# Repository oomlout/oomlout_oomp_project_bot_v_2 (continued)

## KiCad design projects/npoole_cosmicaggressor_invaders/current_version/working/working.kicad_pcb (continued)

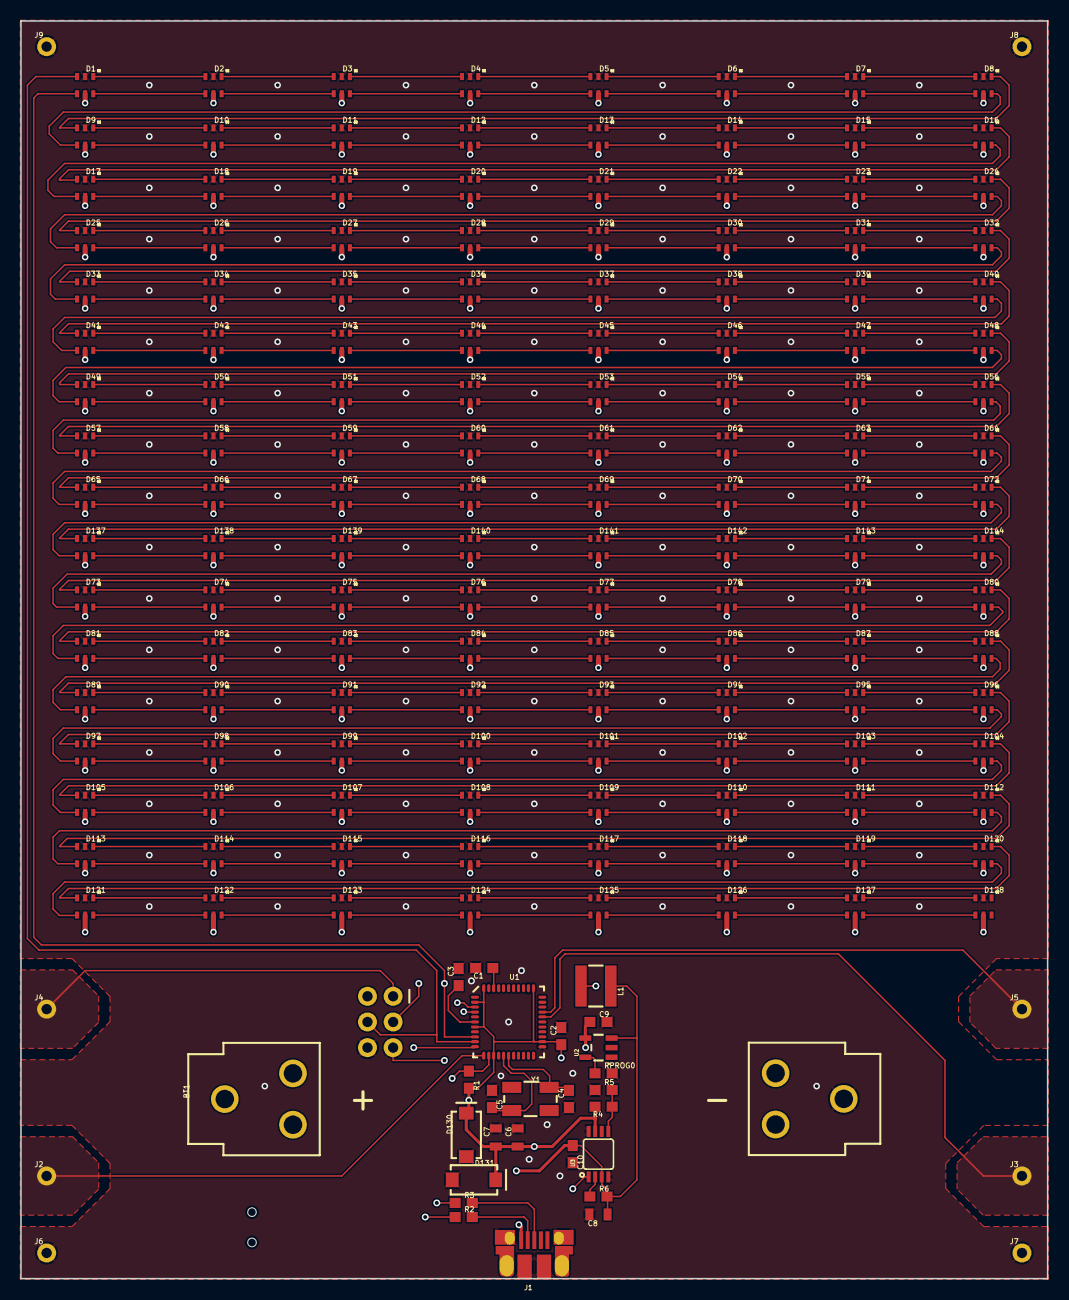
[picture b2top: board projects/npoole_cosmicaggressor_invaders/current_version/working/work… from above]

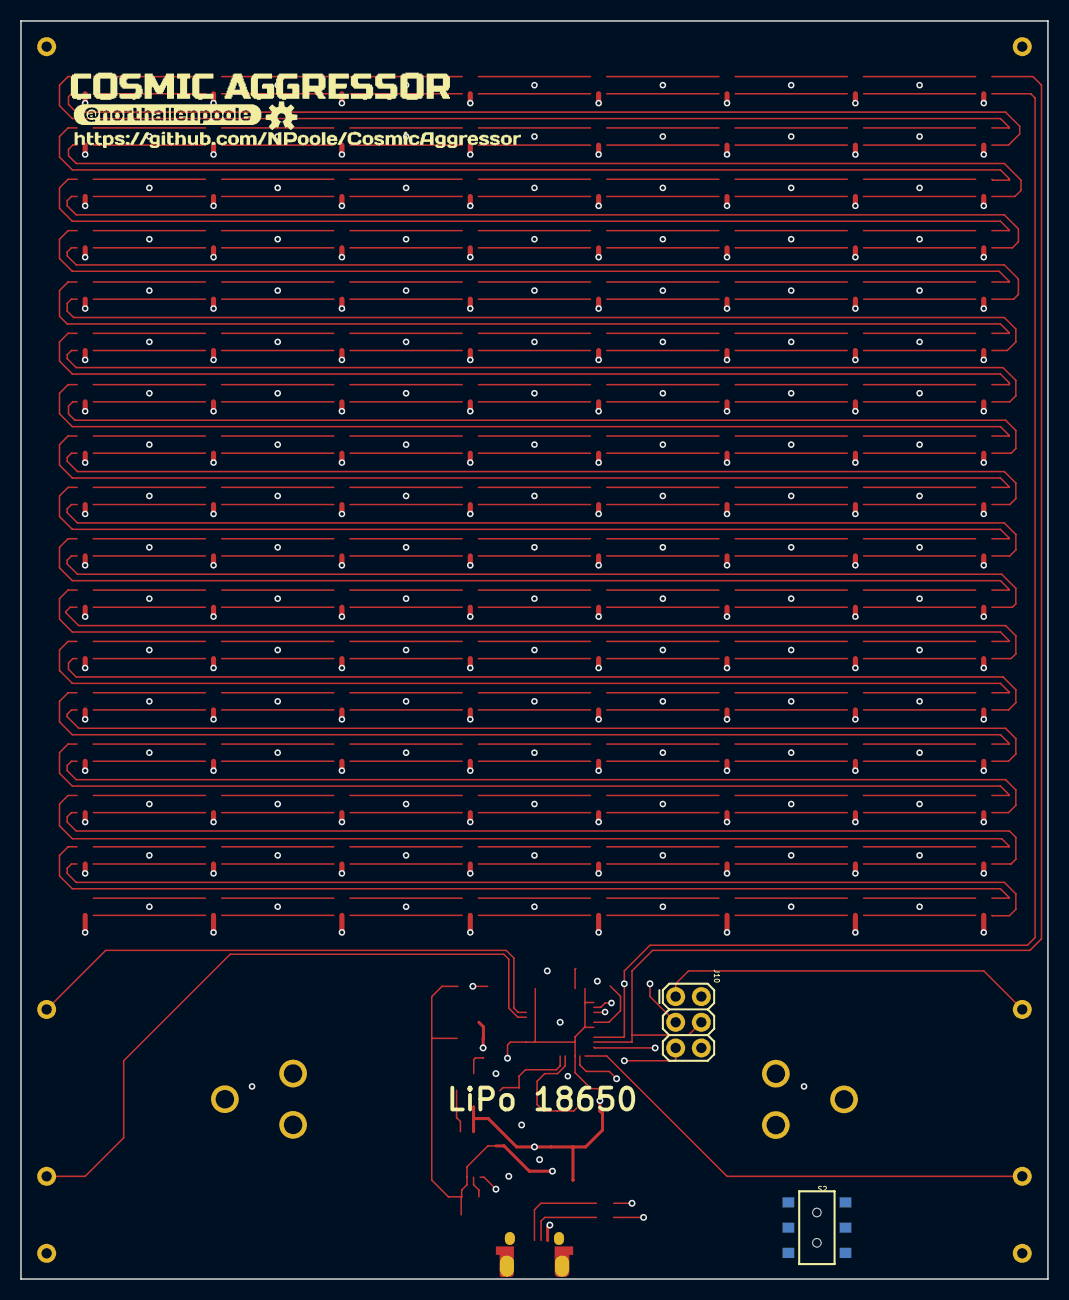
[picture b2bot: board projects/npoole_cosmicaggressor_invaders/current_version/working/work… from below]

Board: 4 copper layers, 101.6 x 124.5 mm, 176 parts (6 on the bottom side), 294 nets.

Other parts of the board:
U$1: COSMIC_AGGRESSOR0
U$2: #NORTHALLENPOOLE1
U$3: HTTPS###GITHUB#COM#NPOOLE#COSMICAGGRESSOR2
U$4: OSHW-LOGO-S

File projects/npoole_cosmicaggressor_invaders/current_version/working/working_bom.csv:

"Id";"Designator";"Footprint";"Quantity";"Designation";"Supplier and ref";
1;"D72,D84,D8,D46,D67,D22,D29,D92,D126,D20,D68,D66,D52,D87,D108,D99,D95,D2,D57,D100,D127,D120,D117,D38,D102,D137,D31,D61,D17,D3,D65,D121,D37,D30,D85,D103,D98,D33,D140,D79,D41,D1,D81,D77,D40,D11,D75,D19,D47,D74,D62,D49,D93,D128,D109,D141,D143,D42,D56,D54,D71,D115,D78,D111,D124,D114,D110,D50,D144,D24,D26,D5,D107,D35,D4,D76,D43,D28,D7,D104,D45,D101,D63,D90,D122,D60,D51,D15,D55,D16,D116,D48,D39,D80,D34,D23,D32,D123,D112,D12,D96,D105,D10,D142,D58,D113,D9,D25,D125,D106,D94,D53,D86,D139,D36,D118,D18,D44,D13,D64,D73,D59,D138,D69,D21,D6,D27,D82,D70,D119,D91,D89,D97,D88,D83,D14";"APA102-2020";136;"APA102-2020";;;
2;"C9,C10";"0603";2;"4.7uF";;;
3;"U2";"SOT23-5";1;"MCP73831";;;
4;"R3,R2";"0603@1";2;"22";;;
5;"Y1";"CRYSTAL-SMD-5X3.2-4PAD";1;"16MHz";;;
6;"R1";"0603@1";1;"10k";;;
7;"BT1";"BATTERY_18650-HOLDER";1;"";;;
8;"J9,J6,J5,J8,J4,J7,J2,J3";"1X01NS_KIT";8;"";;;
9;"D131,D130";"SMA-DIODE";2;"3A/40V/500mV";;;
10;"C2,C3";"0603";2;"1.0uF";;;
11;"C8,C6,C7";"0805";3;"22uF";;;
12;"C4,C5";"0603";2;"18pF";;;
13;"R6,R4";"0603";2;"750K";;;
14;"RPROG0";"0603";1;"2.0k";;;
15;"R5";"0603";1;"100k";;;
16;"C1";"0603";1;"0.1uF";;;
17;"U3";"MSOP8";1;"PAM2401";;;
18;"L1";"INDUCTOR_4X4MM";1;"2.2UH3A";;;
19;"J1";"USB-MICROB-PTH-MILL";1;"";;;
20;"U1";"QFN-44-NOPAD_1_1-LESS_PASTE";1;"32U4";;;
21;"S2";"SWITCH_DPDT_SMD_AYZ0202";1;"";;;
22;"U$1";"COSMIC_AGGRESSOR0";1;"";;;
23;"J10";"2X3";1;"AVR_SPI_PROG_3X2PTH";;;
24;"U$2";"#NORTHALLENPOOLE1";1;"";;;
25;"U$4";"OSHW-LOGO-S";1;"";;;
26;"U$3";"HTTPS###GITHUB#COM#NPOOLE#COSMICAGGRESSOR2";1;"";;;

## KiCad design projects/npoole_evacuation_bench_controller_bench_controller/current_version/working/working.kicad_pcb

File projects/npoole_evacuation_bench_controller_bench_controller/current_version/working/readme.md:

# evacuation_bench_controller
 
## summary 
* id: npoole_evacuation_bench_controller_bench_controller
* user: npoole
* name: evacuation_bench_controller
* board: bench_controller
* repo: https://github.com/NPoole/Evacuation_Bench_Controller

* src_file_repo_sch: 
* src_file_repo_sch_link: https://github.com/NPoole/Evacuation_Bench_Controller/tree/main/
* full details link: https://github.com/oomlout/oomlout_oomp_project_bot_v_2/tree/main/projects/npoole_evacuation_bench_controller_bench_controller/current_version/working  

## schematic  
  
[schematic (pdf)](working_schematic.pdf) 

## pcb  

[board (pdf)](working.pdf)  

## working_bom
| Id | Designator | Footprint | Quantity | Designation | Supplier and ref |  | None | 
| --- | --- | --- | --- | --- | --- | --- | --- | 
| 1 | U$23 | AUTO_EVAC0 | 1 |  |  |  | [''] | 
| 2 | D17,D18,D26,D13,D25,D19,D12,D10,D14,D22,D15,D24,D20,D21,D11,D16,D9 | APA102-2020 | 17 | APA102-2020 |  |  | [''] | 
| 3 | U$26 | EVAC_PORT0 | 1 |  |  |  | [''] | 
| 4 | S4,S5,S3,S8,S2,S7,S1 | CHERRY-MX-LED-1U | 7 | MECHANICAL-KEYBOARD1U |  |  | [''] | 
| 5 | U$18 | ROUGH_PUMP_ON0 | 1 |  |  |  | [''] | 
| 6 | U$27 | PRESSURE0 | 1 |  |  |  | [''] | 
| 7 | U$14 | EVAC_PORT_ISOLATE0 | 1 |  |  |  | [''] | 
| 8 | U$17 | TURBO_ON0 | 1 |  |  |  | [''] | 
| 9 | U$7 | AUX0 | 1 |  |  |  | [''] | 
| 10 | U$25,U$1 | ROUGH0 | 2 |  |  |  | [''] | 
| 11 | U$6 | PORT0 | 1 |  |  |  | [''] | 
| 12 | J13,J9,J11,J12,J4,J6,J5,J7 | 1X02_NO_SILK | 8 |  |  |  | [''] | 
| 13 | FRAME1 | CREATIVE_COMMONS | 1 | FRAME-LEDGER |  |  | [''] | 
| 14 | U$2 | TURBO0 | 1 |  |  |  | [''] | 
| 15 | U$50 | INTEG#SVG0 | 1 |  |  |  | [''] | 
| 16 | U$24,U$4 | VENT0 | 2 |  |  |  | [''] | 
| 17 | U$15 | FULL_VAC_OK0 | 1 |  |  |  | [''] | 
| 18 | U$29 | ROUGH_VAC0 | 1 |  |  |  | [''] | 
| 19 | U$10 | AUTO0 | 1 |  |  |  | [''] | 
| 20 | U$8 | ON0 | 1 |  |  |  | [''] | 
| 21 | U$20 | WATCHDOG_OK0 | 1 |  |  |  | [''] | 
| 22 | S6 | SWITCH_SPDT_PTH_11.6X4.0MM | 1 |  |  |  | [''] | 
| 23 | J10,J8,J2,J1,J3 | 1X03_NO_SILK | 5 |  |  |  | [''] | 
| 24 | U$12 | SHUT_DOWN0 | 1 |  |  |  | [''] | 
| 25 | U$28 | HIGH_VAC0 | 1 |  |  |  | [''] | 
| 26 | U$22 | ISOLATE0 | 1 |  |  |  | [''] | 
| 27 | D23 | LED_5MM | 1 |  |  |  | [''] | 
| 28 | U$11 | BRING_UP0 | 1 |  |  |  | [''] | 
| 29 | U$21 | WAIT_FOR_ION_GAUGE0 | 1 |  |  |  | [''] | 
| 30 | U$19 | TURBO_FULL_SPEED0 | 1 |  |  |  | [''] | 
| 31 | U$13 | SCRAM0 | 1 |  |  |  | [''] | 
| 32 | U$51 | EC#10 | 1 |  |  |  | [''] | 
| 33 | U$5 | EVAC0 | 1 |  |  |  | [''] | 
| 34 | U$16 | ROUGH_PRESSURE0 | 1 |  |  |  | [''] | 
| 35 | @HOLE0,@HOLE2,@HOLE1,@HOLE3 |  | 4 |  |  |  | [''] | 
| 36 | U$30 | AMBIENT0 | 1 |  |  |  | [''] | 
| 37 | U$3 | FORELINE0 | 1 |  |  |  | [''] | 
| 38 | U$9 | OFF0 | 1 |  |  |  | [''] | 
| 39 | U$33 | ADC30 | 1 |  |  |  | [''] | 
| 40 | R14,R7,R12,R15,R16,R9,R11,R5,R3,R13,R10 | 0603 | 11 | 10k |  |  | [''] | 
| 41 | D7,D6,D5,D8 | SOD-323 | 4 | 3A/10V/280mV |  |  | [''] | 
| 42 | Q2,Q1,Q3 | SO08 | 3 | 6.5A/30V/38mÎ© |  |  | [''] | 
| 43 | U$42,U$44,U$43,U$45 | _##10V##_0 | 4 |  |  |  | [''] | 
| 44 | U$36 | ADC00 | 1 |  |  |  | [''] | 
| 45 | R6,R8,R4 | 0603 | 3 | 1M |  |  | [''] | 
| 46 | U$34 | ADC20 | 1 |  |  |  | [''] | 
| 47 | U$31 | ADC50 | 1 |  |  |  | [''] | 
| 48 | D3,D4,D2 | SOD-323 | 3 | 250mA/100V |  |  | [''] | 
| 49 | U$49 | VALVE30 | 1 |  |  |  | [''] | 
| 50 | U$35 | ADC10 | 1 |  |  |  | [''] | 
| 51 | U$37 | GPIO00 | 1 |  |  |  | [''] | 
| 52 | B1 | UNO_R3_SHIELD_NOLABELS | 1 | ARDUINO_UNO_R3_SHIELDNOLABELS |  |  | [''] | 
| 53 | U$46 | 24VDC_IN0 | 1 |  |  |  | [''] | 
| 54 | R17 | 0603 | 1 | 1k |  |  | [''] | 
| 55 | U$39 | 5VDC_IN0 | 1 |  |  |  | [''] | 
| 56 | U$32 | ADC40 | 1 |  |  |  | [''] | 
| 57 | U$38 | GPIO10 | 1 |  |  |  | [''] | 
| 58 | U$48 | VALVE20 | 1 |  |  |  | [''] | 
| 59 | U$41,U$40 | _##5V##_0 | 2 |  |  |  | [''] | 
| 60 | U$47 | VALVE10 | 1 |  |  |  | [''] | 

## bom_schematic
| Ref | Qnty | Value | Cmp name | Footprint | Description | Vendor | DNP | 
| --- | --- | --- | --- | --- | --- | --- | --- | 
| B1 | 1 | ARDUINO_UNO_R3_SHIELDNOLABELS | ARDUINO_UNO_R3_SHIELDNOLABELS | working:UNO_R3_SHIELD_NOLABELS |  |  |  | 
| D2, D3, D4 | 3 | DIODE-BAS16J | DIODE-BAS16J | working:SOD-323 |  |  |  | 
| D5, D6, D7, D8 | 4 | 3A/10V/280mV | DIODE-SCHOTTKY-BAT60A | working:SOD-323 |  |  |  | 
| D9, D10, D11, D12, D13, D14, D15, D16, D17, D18, D19, D20, D21, D22, D24, D25, D26 | 17 | APA102-2020 | APA102-2020 | working:APA102-2020 |  |  |  | 
| D23 | 1 | LED5MM | LED5MM | working:LED_5MM |  |  |  | 
| FRAME1 | 1 | FRAME-LEDGER | FRAME-LEDGER | working:CREATIVE_COMMONS |  |  |  | 
| J1, J2, J3, J8, J10 | 5 | CONN_031X03_NO_SILK | CONN_031X03_NO_SILK | working:1X03_NO_SILK |  |  |  | 
| J4, J5, J6, J7, J9, J11, J12, J13 | 8 | CONN_021X02_NO_SILK | CONN_021X02_NO_SILK | working:1X02_NO_SILK |  |  |  | 
| Q1, Q2, Q3 | 3 | MOSFET-NCH-FDS6630A | MOSFET-NCH-FDS6630A | working:SO08 |  |  |  | 
| R3, R5, R7, R9, R10, R11, R12, R13, R14, R15, R16 | 11 | 10KOHM-0603-1/10W-1% | 10KOHM-0603-1/10W-1% | working:0603 |  |  |  | 
| R4, R6, R8 | 3 | 1MOHM-0603-1/4W-5% | 1MOHM-0603-1/4W-5% | working:0603 |  |  |  | 
| R17 | 1 | 1KOHM-0603-1/10W-1% | 1KOHM-0603-1/10W-1% | working:0603 |  |  |  | 
| S1, S2, S3, S4, S5, S7, S8 | 7 | MECHANICAL-KEYBOARD1U | MECHANICAL-KEYBOARD1U | working:CHERRY-MX-LED-1U |  |  |  | 
| S6 | 1 | SWITCH-SPDT-PTH-11.6X4.0MM | SWITCH-SPDT-PTH-11.6X4.0MM | working:SWITCH_SPDT_PTH_11.6X4.0MM |  |  |  |

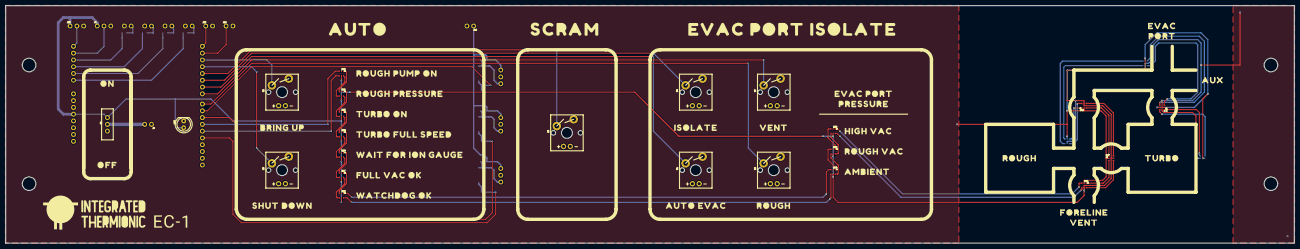
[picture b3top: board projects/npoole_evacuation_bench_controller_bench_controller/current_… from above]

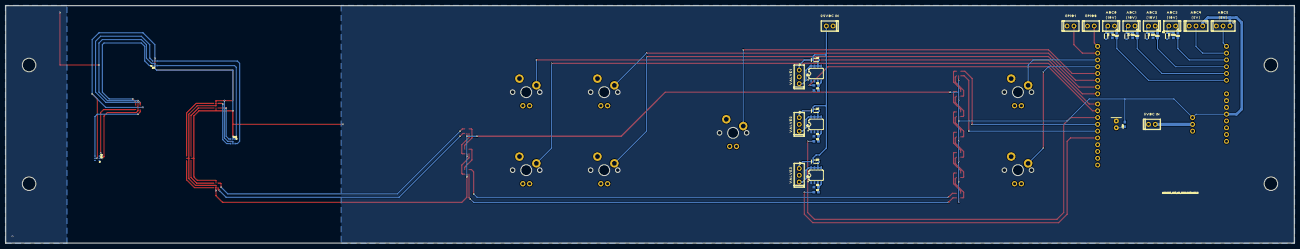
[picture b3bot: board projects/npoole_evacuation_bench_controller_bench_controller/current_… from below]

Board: 2 copper layers, 482.6 x 88.9 mm, 121 parts (55 on the bottom side), 67 nets.

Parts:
@HOLE0, @HOLE1, @HOLE2, @HOLE3: (no value)
B1: ARDUINO_UNO_R3_SHIELDNOLABELS; UNO_R3_SHIELD_NOLABELS
D2, D3, D4: 250mA/100V; SOD-323
D5, D6, D7, D8: 3A/10V/280mV; SOD-323
D9, D10, D11, D12, D13, D14, D15, D16, D17, D18, D19, D20, D21, D22, D24, D25, D26: APA102-2020
D23: LED_5MM
FRAME1: FRAME-LEDGER; CREATIVE_COMMONS
J1, J2, J3, J8, J10: 1X03_NO_SILK
J4, J5, J6, J7, J9, J11, J12, J13: 1X02_NO_SILK
Q1, Q2, Q3: 6.5A/30V/38mΩ; SO08
R3, R5, R7, R9, R10, R11, R12, R13, R14, R15, R16: 10k; 0603
R4, R6, R8: 1M; 0603
R17: 1k; 0603
S1, S2, S3, S4, S5, S7, S8: MECHANICAL-KEYBOARD1U; CHERRY-MX-LED-1U
S6: SWITCH_SPDT_PTH_11.6X4.0MM
U$1, U$25: ROUGH0
U$2: TURBO0
U$3: FORELINE0
U$4, U$24: VENT0
U$5: EVAC0
U$6: PORT0
U$7: AUX0
U$8: ON0
U$9: OFF0
U$10: AUTO0
U$11: BRING_UP0
U$12: SHUT_DOWN0
U$13: SCRAM0
U$14: EVAC_PORT_ISOLATE0
U$15: FULL_VAC_OK0
U$16: ROUGH_PRESSURE0
U$17: TURBO_ON0
U$18: ROUGH_PUMP_ON0
U$19: TURBO_FULL_SPEED0
U$20: WATCHDOG_OK0
U$21: WAIT_FOR_ION_GAUGE0
U$22: ISOLATE0
U$23: AUTO_EVAC0
U$26: EVAC_PORT0
U$27: PRESSURE0
U$28: HIGH_VAC0
U$29: ROUGH_VAC0
U$30: AMBIENT0
U$31: ADC50
U$32: ADC40
U$33: ADC30
U$34: ADC20
U$35: ADC10
U$36: ADC00
U$37: GPIO00
U$38: GPIO10
U$39: 5VDC_IN0
U$40, U$41: _##5V##_0
U$42, U$43, U$44, U$45: _##10V##_0
U$46: 24VDC_IN0
U$47: VALVE10
U$48: VALVE20
U$49: VALVE30
U$50: INTEG#SVG0
U$51: EC#10

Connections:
5V: B1.5V, D9.VDD, D10.VDD, D11.VDD, D12.VDD, D13.VDD, D14.VDD, D15.VDD, D16.VDD, D17.VDD, D18.VDD, D19.VDD, D20.VDD, D21.VDD, D22.VDD, D24.VDD, D25.VDD, D26.VDD, J8.1, J10.1, R17.2, S6.1
ADC0: B1.A0, R9.1, R10.2
ADC1: B1.A1, R11.1, R12.2
ADC2: B1.A2, R13.1, R14.2
ADC3: B1.A3, R15.1, R16.2
ADC4: B1.A4, J8.2
ADC5: B1.A5, J10.2
ANALOG_IN_0: D5.C, J4.2, R9.2
ANALOG_IN_1: D6.C, J5.2, R11.2
ANALOG_IN_2: D7.C, J6.2, R13.2
ANALOG_IN_3: D8.C, J7.2, R15.2
APA102CLK: B1.D12, D22.CKI
APA102DATA: B1.D11, D22.SDI
AUTOEVAC: B1.D6, S1.S1
BRINGUP: B1.D2, S2.S1
GND: B1.GND@0, B1.GND@1, B1.GND@2, D5.A, D6.A, D7.A, D8.A, D9.GND, D10.GND, D11.GND, D12.GND, D13.GND, D14.GND, D15.GND, D16.GND, D17.GND, D18.GND, D19.GND, D20.GND, D21.GND, D22.GND, D23.K, D24.GND, D25.GND, D26.GND, J4.1, J5.1, J6.1, J7.1, J8.3, J9.1, J10.3, J11.2, J12.2, J13.2, Q1.1, Q1.2, Q1.3, Q2.1, Q2.2, Q2.3, Q3.1, Q3.2, Q3.3, R4.1, R6.1, R8.1, R10.1, R12.1, R14.1, R16.1, S1.S2, S2.S2, S3.S2, S4.S2, S5.S2, S7.S2, S8.S2
GPIO0: B1.RX, J13.1
GPIO1: B1.TX, J12.1
ISOLATE: B1.D5, S4.S1
unnamed: Q1.4, R3.2, R4.2
unnamed: Q2.4, R5.2, R6.2
unnamed: D2.A, J1.3, Q1.5, Q1.6, Q1.7, Q1.8
unnamed: D3.A, J2.3, Q2.5, Q2.6, Q2.7, Q2.8
unnamed: Q3.4, R7.2, R8.2
unnamed: D4.A, J3.3, Q3.5, Q3.6, Q3.7, Q3.8
unnamed: D21.CKI, D22.CKO
unnamed: J9.2, S6.2
unnamed: D23.A, R17.1
unnamed: D21.SDI, D22.SDO
unnamed: D20.CKI, D21.CKO
unnamed: D20.SDI, D21.SDO
unnamed: D19.CKI, D20.CKO
unnamed: D19.SDI, D20.SDO
unnamed: D18.CKI, D19.CKO
unnamed: D18.SDI, D19.SDO
unnamed: D17.CKI, D18.CKO
unnamed: D17.SDI, D18.SDO
unnamed: D10.CKI, D17.CKO
unnamed: D10.SDI, D17.SDO
unnamed: D10.CKO, D24.CKI
unnamed: D10.SDO, D24.SDI
unnamed: D24.CKO, D25.CKI
unnamed: D24.SDO, D25.SDI
unnamed: D25.CKO, D26.CKI
unnamed: D25.SDO, D26.SDI
unnamed: D14.CKI, D26.CKO
unnamed: D14.SDI, D26.SDO
unnamed: D13.CKI, D14.CKO
unnamed: D13.SDI, D14.SDO
unnamed: D12.CKI, D13.CKO
unnamed: D12.SDI, D13.SDO
unnamed: D12.CKO, D16.CKI
unnamed: D12.SDO, D16.SDI
unnamed: D9.CKI, D16.CKO
unnamed: D9.SDI, D16.SDO
unnamed: D9.CKO, D15.CKI
unnamed: D9.SDO, D15.SDI
unnamed: D11.CKI, D15.CKO
unnamed: D11.SDI, D15.SDO
ROUGH: B1.D8, S8.S1
SCRAM: B1.D4, S5.S1
SHUTDOWN: B1.D3, S3.S1
VALVE1: B1.D9, R3.1
VALVE2: B1.D10, R5.1
VALVE3: B1.D13, R7.1
VCC_2: D2.C, D3.C, D4.C, J1.1, J2.1, J3.1, J11.1
VENT: B1.D7, S7.S1

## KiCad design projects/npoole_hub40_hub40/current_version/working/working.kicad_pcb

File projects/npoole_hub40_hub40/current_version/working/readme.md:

# hub40
 
## summary 
* id: npoole_hub40_hub40
* user: npoole
* name: hub40
* board: hub40
* repo: https://github.com/NPoole/HUB40

* src_file_repo_sch: 
* src_file_repo_sch_link: https://github.com/NPoole/HUB40/tree/master/
* full details link: https://github.com/oomlout/oomlout_oomp_project_bot_v_2/tree/main/projects/npoole_hub40_hub40/current_version/working  

## schematic  
  
[schematic (pdf)](working_schematic.pdf) 

## pcb  

[board (pdf)](working.pdf)  

## working_bom
| Id | Designator | Footprint | Quantity | Designation | Supplier and ref |  | None | 
| --- | --- | --- | --- | --- | --- | --- | --- | 
| 1 | SW37,SW31,SW19,SW24,SW6,SW15,SW25,SW18,SW5,SW23,SW46,SW39,SW30,SW22,SW26,SW38,SW48,SW43,SW8,SW28,SW33,SW16,SW35,SW17,SW4,SW20,SW10,SW34,SW29,SW21,SW41,SW13,SW40,SW11,SW7,SW2,SW14,SW36,SW12,SW32,SW47,SW1,SW45,SW3,SW9,SW27 | MX1A-XXNW | 46 |  |  |  | [''] | 
| 2 | G1,G3,G2 | USB_A_VERT | 3 | USB_A_VERT |  |  | [''] | 
| 3 | U$3,U$1,U$4,U$2 | STAND-OFF | 4 |  |  |  | [''] | 
| 4 | J2 | USB-C-16P | 1 |  |  |  | [''] | 
| 5 | D12,D21,D37,D26,D2,D34,D22,D45,D5,D15,D36,D29,D39,D19,D47,D17,D10,D8,D44,D1,D23,D42,D18,D48,D9,D27,D16,D20,D43,D24,D3,D41,D6,D13,D38,D25,D28,D40,D4,D35,D11,D31,D46,D7,D14,D33 | SOD-323 | 46 | 250mA/100V |  |  | [''] | 
| 6 | R7,R8,R3,R2,R10,R5,R4,R6,R11,R9 | 0603 | 10 | 22 |  |  | [''] | 
| 7 | R1,R13 | 0603 | 2 | 10k |  |  | [''] | 
| 8 | U2 | QFN-28-5MM-1_1 | 1 | USB_HUB_4_PORT |  |  | [''] | 
| 9 | R16,R15 | 0603 | 2 | 5.1k |  |  | [''] | 
| 10 | C2,C6,C1,C5 | 0603 | 4 | 18pF |  |  | [''] | 
| 11 | U1 | QFN-44-NOPAD_1_1 | 1 | 32U4 |  |  | [''] | 
| 12 | Y2 | CRYSTAL-SMD-5X3.2-4PAD | 1 | 12MHz |  |  | [''] | 
| 13 | R12 | 0603 | 1 | 649 |  |  | [''] | 
| 14 | F1 | 1206 | 1 | 6V/0.5A |  |  | [''] | 
| 15 | Y1 | CRYSTAL-SMD-5X3.2-4PAD | 1 | 16MHz |  |  | [''] | 
| 16 | C4 | 0603 | 1 | 1.0uF |  |  | [''] | 
| 17 | C3 | 0603 | 1 | 0.1uF |  |  | [''] | 
| 18 | U$5 | HUB400 | 1 |  |  |  | [''] | 

## bom_schematic
| Ref | Qnty | Value | Cmp name | Footprint | Description | Vendor | DNP | 
| --- | --- | --- | --- | --- | --- | --- | --- | 
| C1, C2, C5, C6 | 4 | 18PF-0603-50V-5% | 18PF-0603-50V-5% | working:0603 |  |  |  | 
| C3 | 1 | 0.1UF-0603-25V-(+80/-20%) | 0.1UF-0603-25V-(+80/-20%) | working:0603 |  |  |  | 
| C4 | 1 | 1.0UF-0603-16V-10% | 1.0UF-0603-16V-10% | working:0603 |  |  |  | 
| D1, D2, D3, D4, D5, D6, D7, D8, D9, D10, D11, D12, D13, D14, D15, D16, D17, D18, D19, D20, D21, D22, D23, D24, D25, D26, D27, D28, D29, D31, D33, D34, D35, D36, D37, D38, D39, D40, D41, D42, D43, D44, D45, D46, D47, D48 | 46 | DIODE-BAS16J | DIODE-BAS16J | working:SOD-323 |  |  |  | 
| F1 | 1 | PPTC_6V500MA-2 | PPTC_6V500MA-2 | working:1206 |  |  |  | 
| G1, G2, G3 | 3 | USB_A_VERT | USB_A_VERT | working:USB_A_VERT |  |  |  | 
| J2 | 1 | USB_C2-LAYER | USB_C2-LAYER | working:USB-C-16P |  |  |  | 
| R1, R13 | 2 | 10KOHM-0603-1/10W-1% | 10KOHM-0603-1/10W-1% | working:0603 |  |  |  | 
| R2, R3, R4, R5, R6, R7, R8, R9, R10, R11 | 10 | 22OHM-0603-1/10W-1% | 22OHM-0603-1/10W-1% | working:0603 |  |  |  | 
| R12 | 1 | 680OHM-0603-1/10W-5% | 680OHM-0603-1/10W-5% | working:0603 |  |  |  | 
| R15, R16 | 2 | 5.1k | 5.1KOHM5.1KOHM-0603-1/10W-1% | working:0603 |  |  |  | 
| SW1, SW2, SW3, SW4, SW5, SW6, SW7, SW8, SW9, SW10, SW11, SW12, SW13, SW14, SW15, SW16, SW17, SW18, SW19, SW20, SW21, SW22, SW23, SW24, SW25, SW26, SW27, SW28, SW29, SW30, SW31, SW32, SW33, SW34, SW35, SW36, SW37, SW38, SW39, SW40, SW41, SW43, SW45, SW46, SW47, SW48 | 46 | CHERRY_MX_WITH_FIXING_PINS | CHERRY_MX_WITH_FIXING_PINS | working:MX1A-XXNW |  |  |  | 
| U1 | 1 | ATMEGA32U41:1 | ATMEGA32U41{colon}1 | working:QFN-44-NOPAD_1_1 |  |  |  | 
| U2 | 1 | USB_HUB_4_PORT | USB_HUB_4_PORT | working:QFN-28-5MM-1_1 |  |  |  | 
| Y1 | 1 | 16MHz | CRYSTAL-16MHZSMD-5X3.2 | working:CRYSTAL-SMD-5X3.2-4PAD |  |  |  | 
| Y2 | 1 | 12MHz | CRYSTAL-12MHZ{dblquote} | working:CRYSTAL-SMD-5X3.2-4PAD |  |  |  |

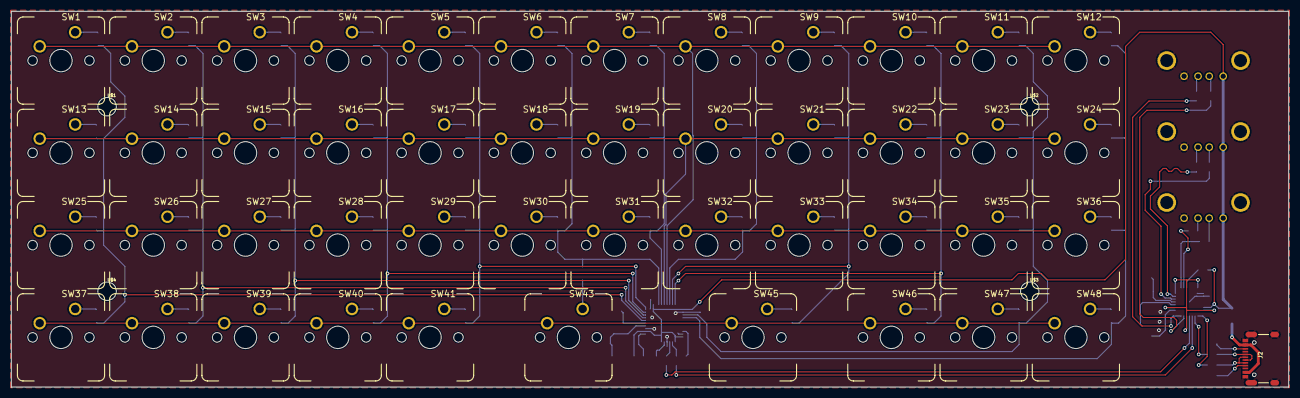
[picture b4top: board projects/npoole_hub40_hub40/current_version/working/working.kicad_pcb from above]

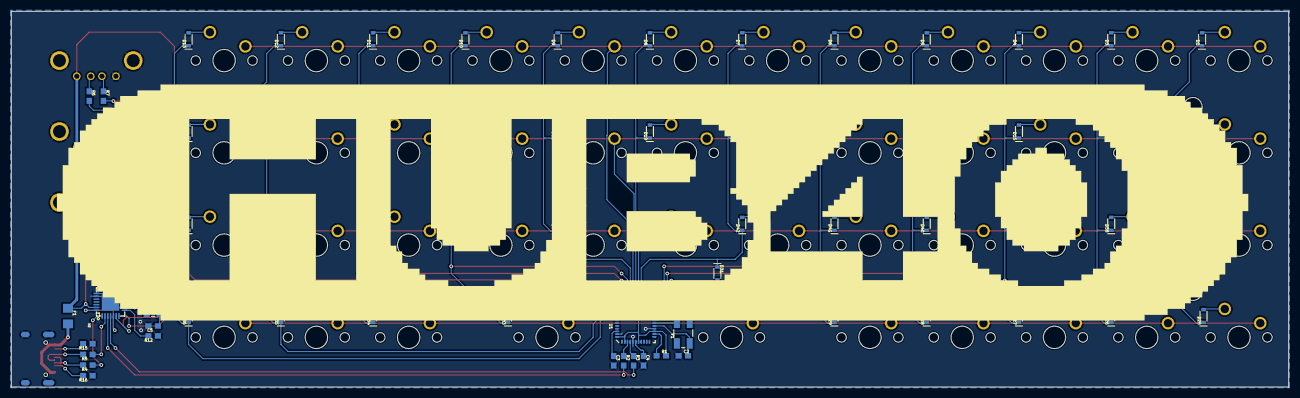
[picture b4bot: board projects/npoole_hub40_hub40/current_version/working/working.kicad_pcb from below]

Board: 2 copper layers, 228.6 x 67.2 mm, 127 parts (73 on the bottom side), 97 nets.

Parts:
C1, C2, C5, C6: 18pF; 0603
C3: 0.1uF; 0603
C4: 1.0uF; 0603
D1, D2, D3, D4, D5, D6, D7, D8, D9, D10, D11, D12, D13, D14, D15, D16, D17, D18, D19, D20, D21, D22, D23, D24, D25, D26, D27, D28, D29, D31, D33, D34, D35, D36, D37, D38, D39, D40, D41, D42, D43, D44, D45, D46, D47, D48: 250mA/100V; SOD-323
F1: 6V/0.5A; 1206
G1, G2, G3: USB_A_VERT
J2: USB-C-16P
R1, R13: 10k; 0603
R2, R3, R4, R5, R6, R7, R8, R9, R10, R11: 22; 0603
R12: 649; 0603
R15, R16: 5.1k; 0603
SW1, SW2, SW3, SW4, SW5, SW6, SW7, SW8, SW9, SW10, SW11, SW12, SW13, SW14, SW15, SW16, SW17, SW18, SW19, SW20, SW21, SW22, SW23, SW24, SW25, SW26, SW27, SW28, SW29, SW30, SW31, SW32, SW33, SW34, SW35, SW36, SW37, SW38, SW39, SW40, SW41, SW43, SW45, SW46, SW47, SW48: MX1A-XXNW
U1: 32U4; QFN-44-NOPAD_1_1
U2: USB_HUB_4_PORT; QFN-28-5MM-1_1
U$1, U$2, U$3, U$4: STAND-OFF
U$5: HUB400
Y1: 16MHz; CRYSTAL-SMD-5X3.2-4PAD
Y2: 12MHz; CRYSTAL-SMD-5X3.2-4PAD

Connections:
2D+: G1.3, R7.1
2D-: G1.2, R6.1
3D+: G2.3, R9.2
3D-: G2.2, R8.2
4D+: G3.3, R11.2
4D-: G3.2, R10.2
COL1: D1.C, D2.C, D25.C, D37.C, U1.18
COL2: D3.C, D14.C, D26.C, D38.C, U1.19
COL3: D4.C, D15.C, D27.C, D39.C, U1.20
COL4: D5.C, D16.C, D28.C, D40.C, U1.21
COL5: D6.C, D17.C, D29.C, D41.C, U1.22
COL6: D7.C, D18.C, D31.C, D42.C, U1.26
COL7: D8.C, D19.C, D43.C, U1.27
COL8: D9.C, D20.C, D44.C, U1.30
COL9: D10.C, D21.C, D33.C, D45.C, U1.31
COL10: D11.C, D22.C, D34.C, D46.C, U1.32
COL11: D12.C, D23.C, D35.C, D47.C, U1.36
COL12: D13.C, D24.C, D36.C, D48.C, U1.37
GND: C1.1, C2.1, C3.2, C4.2, C5.2, C6.2, G1.4, G1.SHIELD_1, G1.SHIELD_2, G2.4, G2.SHIELD_1, G2.SHIELD_2, G3.4, G3.SHIELD_1, G3.SHIELD_2, J2.GND, J2.GND2, J2.SHLD1, J2.SHLD2, J2.SHLD3, J2.SHLD4, J2.SHLD5, J2.SHLD6, J2.SHLD7, J2.SHLD8, R12.1, R15.1, R16.1, U1.5, U1.15, U1.23, U1.33, U1.35, U1.43, U2.P$22, U2.P$23, U2.P$29
HOST-: J2.A7, J2.B7, R4.2
HOST_D+: R5.1, U2.P$2
HOST_D-: R4.1, U2.P$1
KBD+: R3.2, U2.P$4
KBD-: R2.2, U2.P$3
KB_D+: R3.1, U1.4
KB_D-: R2.1, U1.3
unnamed: D2.A, SW1.2
unnamed: D3.A, SW2.2
unnamed: D4.A, SW3.2
unnamed: D5.A, SW4.2
unnamed: D6.A, SW5.2
unnamed: D7.A, SW6.2
unnamed: D8.A, SW7.2
unnamed: D9.A, SW8.2
unnamed: D10.A, SW9.2
unnamed: D11.A, SW10.2
unnamed: D12.A, SW11.2
unnamed: D13.A, SW12.2
unnamed: D1.A, SW13.2
unnamed: D25.A, SW37.2
unnamed: D37.A, SW25.2
unnamed: D38.A, SW26.2
unnamed: D26.A, SW38.2
unnamed: D14.A, SW14.2
unnamed: D15.A, SW15.2
unnamed: D16.A, SW16.2
unnamed: D28.A, SW40.2
unnamed: D27.A, SW39.2
unnamed: D39.A, SW27.2
unnamed: D40.A, SW28.2
unnamed: D41.A, SW29.2
unnamed: D42.A, SW30.2
unnamed: D29.A, SW41.2
unnamed: D17.A, SW17.2
unnamed: D18.A, SW18.2
unnamed: J2.A6, J2.B6, R5.2
unnamed: D43.A, SW31.2
unnamed: D31.A, SW43.2
unnamed: D19.A, SW19.2
unnamed: D23.A, SW23.2
unnamed: D22.A, SW22.2
unnamed: D21.A, SW21.2
unnamed: D20.A, SW20.2
unnamed: J2.A5, R16.2
unnamed: D33.A, SW45.2
unnamed: D34.A, SW46.2
unnamed: D35.A, SW47.2
unnamed: D36.A, SW48.2
unnamed: D24.A, SW24.2
unnamed: D48.A, SW36.2
unnamed: D47.A, SW35.2
unnamed: D46.A, SW34.2
unnamed: D45.A, SW33.2
unnamed: D44.A, SW32.2
unnamed: R1.1, U1.13
unnamed: C3.1, U1.42
unnamed: C1.2, U1.17, Y1.3
unnamed: C2.2, U1.16, Y1.1
unnamed: C4.1, U1.6
unnamed: R6.2, U2.P$6
unnamed: U2.P$5, U2.P$9, U2.P$14, U2.P$21, U2.P$28
unnamed: R7.2, U2.P$7
unnamed: R8.1, U2.P$12
unnamed: R9.1, U2.P$13
unnamed: R10.1, U2.P$15
unnamed: R11.1, U2.P$16
unnamed: C5.1, U2.P$10, Y2.3
unnamed: C6.1, U2.P$11, Y2.1
unnamed: R13.1, U2.P$17
unnamed: F1.2, J2.VBUS1, J2.VBUS2
unnamed: R12.2, U2.P$8
unnamed: J2.B5, R15.2
ROW1: SW1.1, SW2.1, SW3.1, SW4.1, SW5.1, SW6.1, SW7.1, SW8.1, SW9.1, SW10.1, SW11.1, SW12.1, U1.29
ROW2: SW13.1, SW14.1, SW15.1, SW16.1, SW17.1, SW18.1, SW19.1, SW20.1, SW21.1, SW22.1, SW23.1, SW24.1, U1.28
ROW3: SW37.1, SW38.1, SW39.1, SW40.1, SW41.1, SW43.1, SW45.1, SW46.1, SW47.1, SW48.1
ROW4: SW25.1, SW26.1, SW27.1, SW28.1, SW29.1, SW30.1, SW31.1, SW32.1, SW33.1, SW34.1, SW35.1, SW36.1
VCC: F1.1, G1.1, G2.1, G3.1, R1.2, R13.2, U1.2, U1.7, U1.14, U1.24, U1.34, U1.44, U2.P$27
